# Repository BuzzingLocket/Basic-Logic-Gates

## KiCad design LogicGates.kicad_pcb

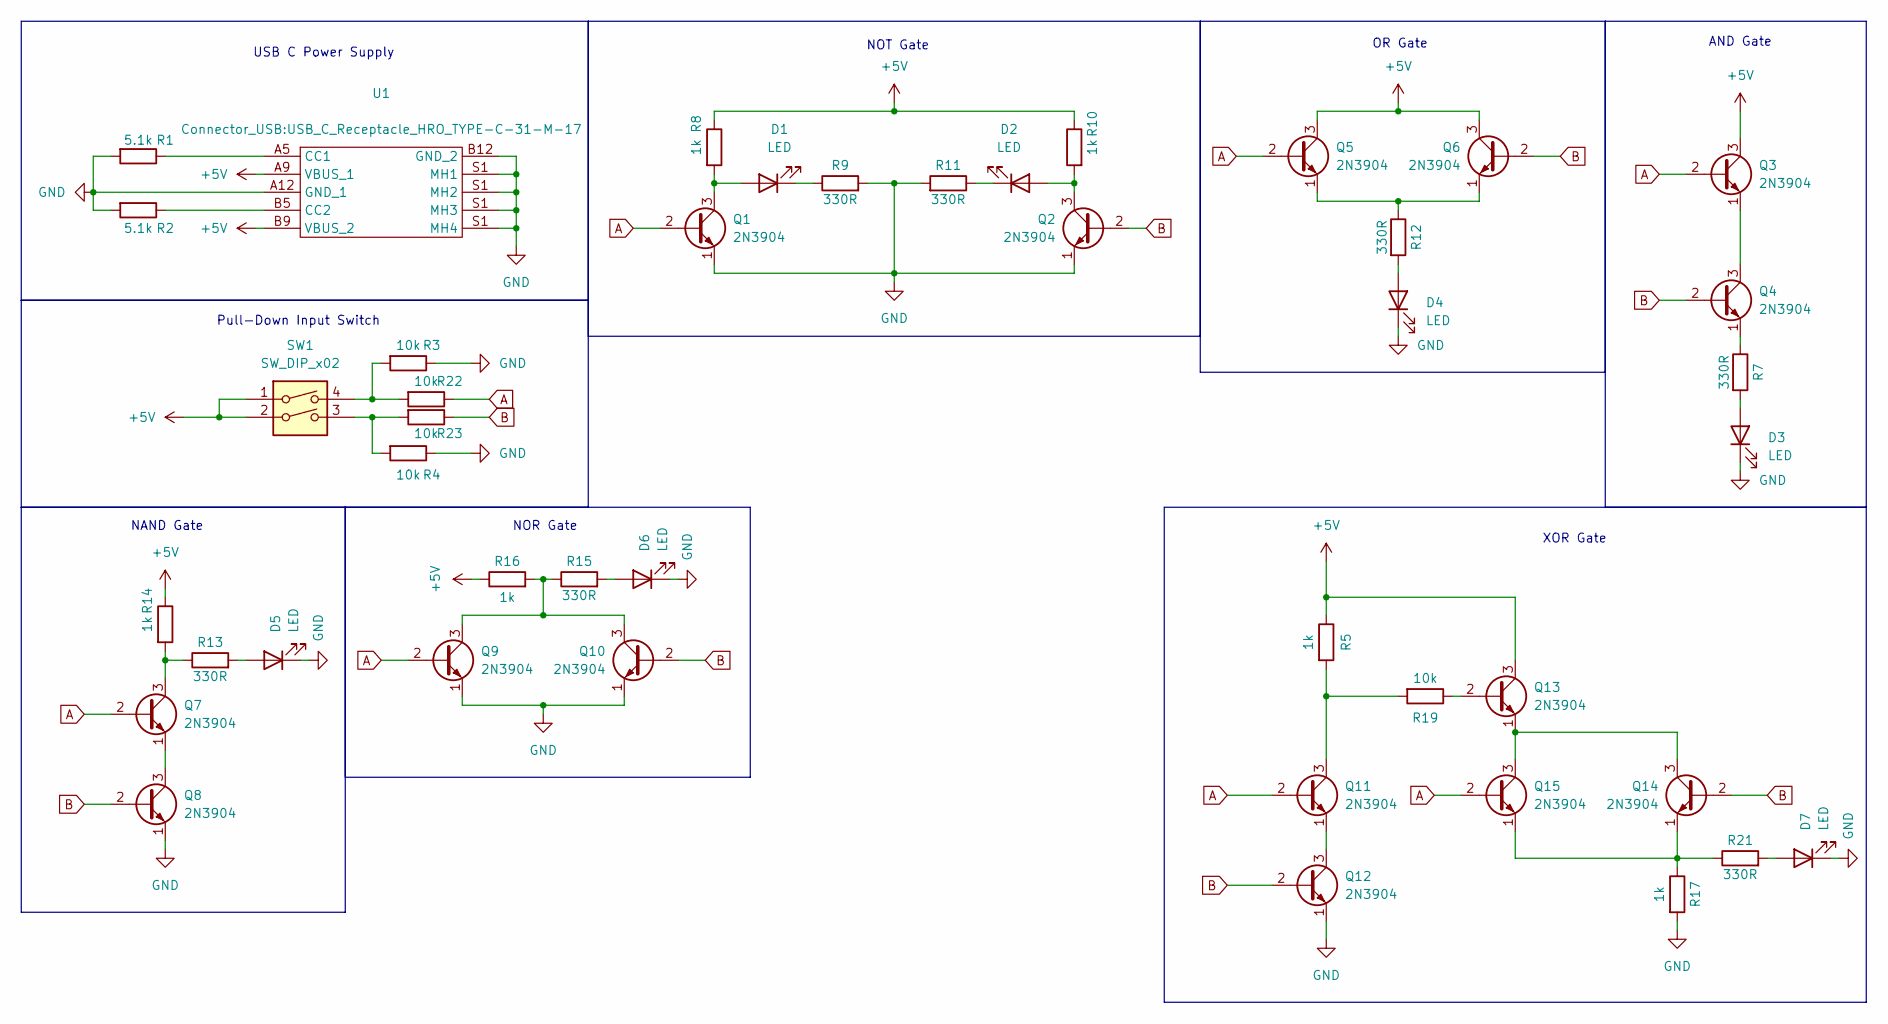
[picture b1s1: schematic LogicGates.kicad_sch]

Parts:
D1, D2, D3, D4, D5, D6, D7: LED; LED_0402_1005Metric
Q1, Q2, Q3, Q4, Q5, Q6, Q7, Q8, Q9, Q10, Q11, Q12, Q13, Q14, Q15: 2N3904; TO-92_Inline
R1, R2: 5.1k; R_0402_1005Metric
R3, R4, R19, R22, R23: 10k; R_0402_1005Metric
R5, R8, R10, R14, R16, R17: 1k; R_0402_1005Metric
R7, R9, R11, R12, R13, R15, R21: 330R; R_0402_1005Metric
SW1: SW_DIP_x02; SW_DIP_SPSTx02_Slide_9.78x7.26mm_W8.61mm_P2.54mm
U1: USB_C_Receptacle_HRO_TYPE-C-31-M-17

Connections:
+5V: Q3.3 (C), Q5.3 (C), Q6.3 (C), Q13.3 (C), R5.1, R8.1, R10.1, R14.1, R16.1, SW1.1, SW1.2, U1.A9 (VBUS_1), U1.B9 (VBUS_2)
A: Q1.2 (B), Q3.2 (B), Q5.2 (B), Q7.2 (B), Q9.2 (B), Q11.2 (B), Q15.2 (B), R22.1
B: Q2.2 (B), Q4.2 (B), Q6.2 (B), Q8.2 (B), Q10.2 (B), Q12.2 (B), Q14.2 (B), R23.1
GND: D3.1 (K), D4.1 (K), D5.1 (K), D6.1 (K), D7.1 (K), Q1.1 (E), Q2.1 (E), Q8.1 (E), Q9.1 (E), Q10.1 (E), Q12.1 (E), R1.2, R2.2, R3.1, R4.1, R9.2, R11.2, R17.2, U1.A12 (GND_1), U1.B12 (GND_2), U1.S1 (MH4)
unnamed: D1.2 (A), Q1.3 (C), R8.2
unnamed: D1.1 (K), R9.1
unnamed: D2.2 (A), Q2.3 (C), R10.2
unnamed: D2.1 (K), R11.1
unnamed: D3.2 (A), R7.2
unnamed: D4.2 (A), R12.2
unnamed: D5.2 (A), R13.2
unnamed: D6.2 (A), R15.2
unnamed: D7.2 (A), R21.2
unnamed: Q3.1 (E), Q4.3 (C)
unnamed: Q4.1 (E), R7.1
unnamed: Q5.1 (E), Q6.1 (E), R12.1
unnamed: Q7.3 (C), R13.1, R14.2
unnamed: Q7.1 (E), Q8.3 (C)
unnamed: Q9.3 (C), Q10.3 (C), R15.1, R16.2
unnamed: Q11.3 (C), R5.2, R19.2
unnamed: Q11.1 (E), Q12.3 (C)
unnamed: Q13.2 (B), R19.1
unnamed: Q13.1 (E), Q14.3 (C), Q15.3 (C)
unnamed: Q14.1 (E), Q15.1 (E), R17.1, R21.1
unnamed: R3.2, R22.2, SW1.4
unnamed: R4.2, R23.2, SW1.3
unnamed: R1.1, U1.A5 (CC1)
unnamed: R2.1, U1.B5 (CC2)

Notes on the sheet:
NOT Gate
OR Gate
XOR Gate
NOR Gate
Pull-Down Input Switch
NAND Gate
AND Gate
USB C Power Supply

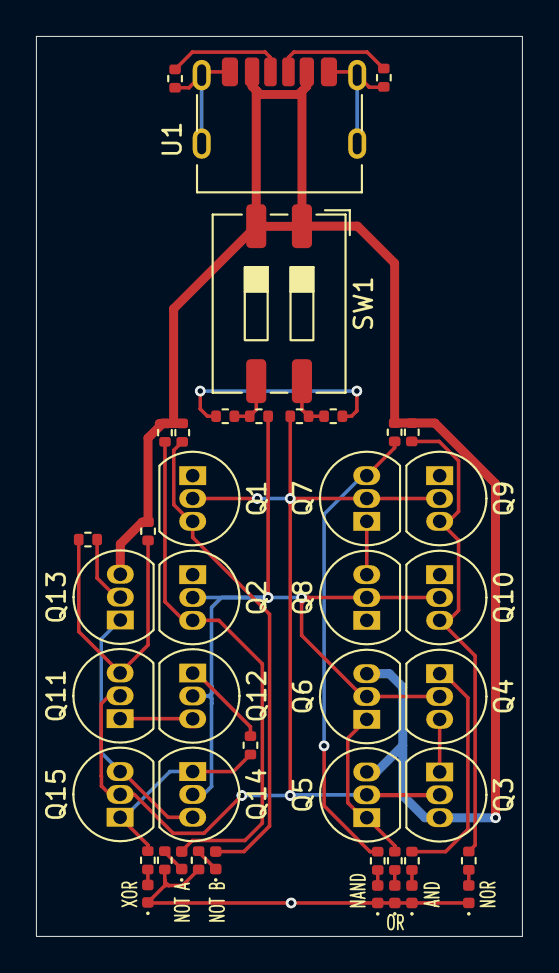
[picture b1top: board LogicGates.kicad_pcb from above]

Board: 2 copper layers, 27.0 x 50.0 mm, 44 parts (0 on the bottom side), 28 nets.
